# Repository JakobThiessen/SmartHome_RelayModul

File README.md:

# SmartHome_RelayModul

Folgende Änderung muss vorgenommen werden:

IO34, IO35, IO36 and IO39 --> input only

IO34 --> IO26 or IO33\
IO35 --> IO27 or IO32

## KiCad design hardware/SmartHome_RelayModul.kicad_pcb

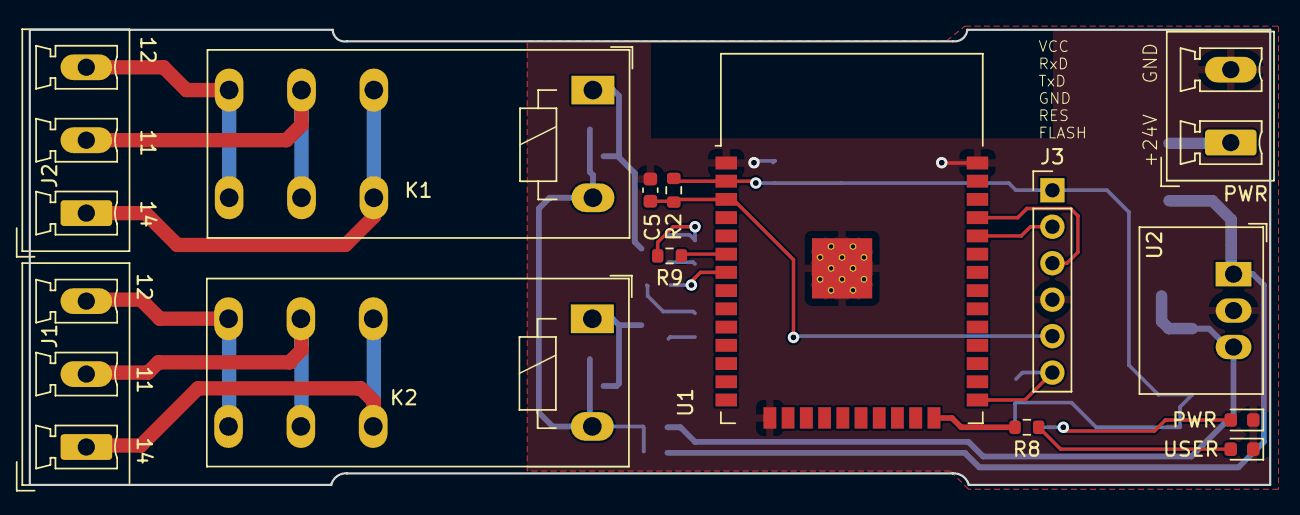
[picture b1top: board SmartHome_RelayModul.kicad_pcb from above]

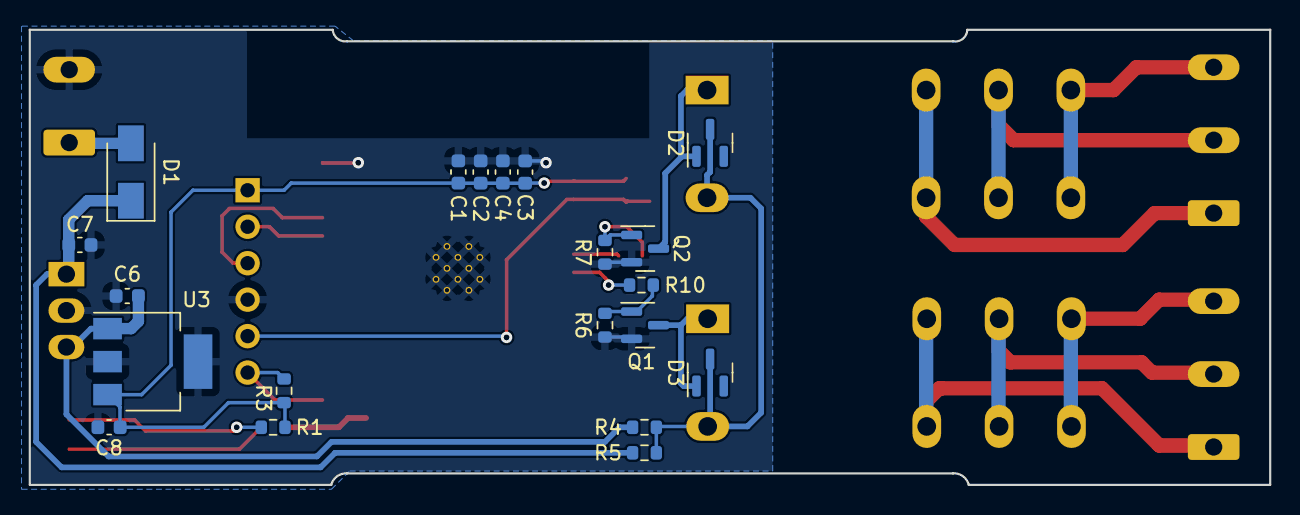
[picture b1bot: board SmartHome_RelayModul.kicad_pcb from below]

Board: 2 copper layers, 86.4 x 31.7 mm, 34 parts (20 on the bottom side), 25 nets.

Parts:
C1, C2, C5: 100nF; C_0603_1608Metric
C3, C4: 1µF; C_0603_1608Metric
C6: 10µF/6,3V; C_0603_1608Metric
C7: 100nF/50V; C_0603_1608Metric
C8: 4,7µF/6,3V; C_0603_1608Metric
D1: ES1D; D_SMA
D2, D3: BAS21; SOT-23
J1, J2: Conn_01x03; PhoenixContact_MCV_1,5_3-G-5.08_1x03_P5.08mm_Vertical
J3: Conn_01x06; PinHeader_1x06_P2.54mm_Vertical
K1, K2: RT314A12; Relay_SPDT_Schrack-RT1-16A-FormC_RM5mm
PWR: Conn_01x02; PhoenixContact_MCV_1,5_2-G-5.08_1x02_P5.08mm_Vertical
PWR#2: green; LED_0603_1608Metric
Q1, Q2: BSS123; SOT-23
R1, R8: 470R; R_0603_1608Metric
R2, R3: 10k; R_0603_1608Metric
R4: 0R0; R_0603_1608Metric
R5: N.P.; R_0603_1608Metric
R6, R7: 100k; R_0603_1608Metric
R9, R10: 100; R_0603_1608Metric
U1: ESP32-WROOM-32D; ESP32-WROOM-32
U2: R-78B5.0-2.0; Converter_DCDC_RECOM_R-78B-2.0_THT
U3: LT1129-3.3_SOT223; SOT-223-3_TabPin2
USER: blue; LED_0603_1608Metric

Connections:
+3.3V: C1.1, C2.1, C3.1, C4.1, C8.1, J3.1, R1.1, R2.1, R3.1, U1.2 (VDD), U3.3 (VO)
+5V: C6.1, R4.1, U2.3 (OUT), U3.1 (VI)
+24V: C7.1, D1.1 (K), R5.1, U2.1 (IN)
/IO0: J3.6, R3.2, U1.25 (IO0)
/IO01: J3.3, U1.35 (TXD0/IO1)
/IO03: J3.2, U1.34 (RXD0/IO3)
/IO34_K1: R9.2, U1.6 (IO34)
/IO35_K2: R10.2, U1.7 (IO35)
/IO_02: R8.1, U1.24 (IO2)
/RST: C5.1, J3.5, R2.2, U1.3 (EN)
GND: C1.2, C2.2, C3.2, C4.2, C5.2, C6.2, C7.2, C8.2, J3.4, PWR.2, PWR#2.1 (K), Q1.2 (S), Q2.2 (S), R6.2, R7.2, U1.1 (GND), U1.15 (GND), U1.38 (GND), U1.39 (GND), U2.2 (GND), U3.2 (GND), USER.1 (K)
unnamed: D1.2 (A), PWR.1
unnamed: D2.1 (A), K1.A1, Q2.3 (D)
unnamed: D3.1 (A), K2.A1, Q1.3 (D)
unnamed: PWR#2.2 (A), R1.2
unnamed: R8.2, USER.2 (A)
unnamed: J1.1, K2.12
unnamed: J1.2, K2.11
unnamed: J1.3, K2.14
unnamed: J2.1, K1.12
unnamed: J2.2, K1.11
unnamed: J2.3, K1.14
unnamed: Q1.1 (G), R6.1, R10.1
unnamed: Q2.1 (G), R7.1, R9.1
Vdrive: D2.3 (K), D3.3 (K), K1.A2, K2.A2, R4.2, R5.2

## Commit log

2022-12-23 initial
2022-12-23 Rename files
2022-12-23 Dokumentation hinzugefügt
2023-08-15 bild hinzugefügt
